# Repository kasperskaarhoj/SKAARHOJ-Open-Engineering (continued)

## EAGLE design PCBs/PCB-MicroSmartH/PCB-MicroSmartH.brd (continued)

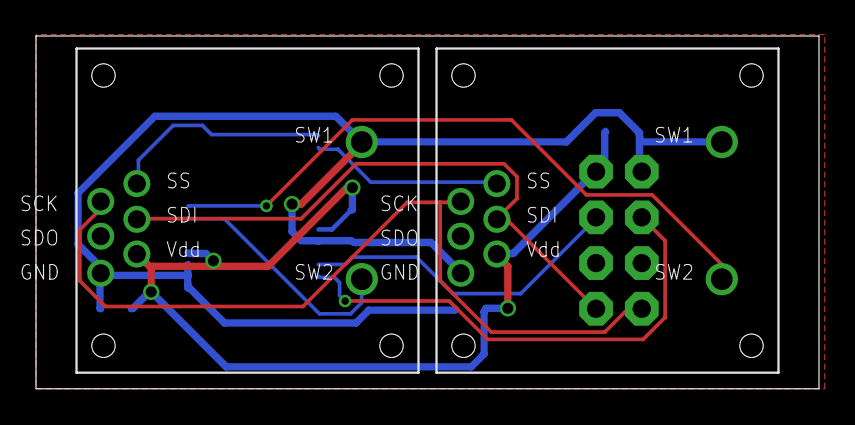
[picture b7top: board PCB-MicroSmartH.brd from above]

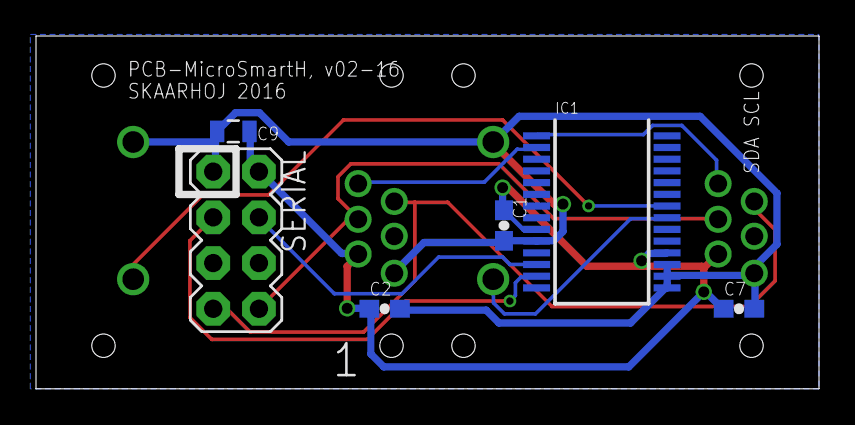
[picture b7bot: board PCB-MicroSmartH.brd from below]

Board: 2 copper layers, 43.5 x 19.6 mm, 8 parts (6 on the bottom side), 10 nets.
